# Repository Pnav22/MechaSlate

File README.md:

# MechaSlate 
**A Custom-Built Mechanical Keyboard**  
by Pranav M

---

## Overview
**MechaSlate** is my first custom mechanical keyboard project, created from scratch with no prior experience. This build taught me PCB design using KiCad, CAD modeling with Fusion 360, and the use of plugins and scripts to place keyswitches

[Watch on YouTube](https://www.youtube.com/shorts/u8ZRRqsj9ko)

I wanted to make this project so I could learn more about electronics and familiarize myself with more forms of engineering. It was really fun!
---

####  Initial Layout Planning
I decided on I wanted to make a keyboard like this 

#### PCB Design

| Schematic |  PCB |
|:--:|:--:|
|  |  |

#### Case Design 
Back and front case modeled for print.

| Back | Front |
|:--:|:--:|
| |  |

Added a staggering Slot pattern for the back!

####  Final Case
Manually placed all keycaps and installed everything.

---

#### Assembly 

It uses **threaded heat-set inserts (M3 x 5mm x 4mm)** for secure mounting. These inserts are installed into the case.

The top and bottom halves of the keyboard are fastened together using **four M3 x 16mm socket head cap screws .

This project has a Gasket Mount 

| Item Name            | Item Source | Quantity | Cost (USD w/ shipping) | Link |
|----------------------|-------------|----------|-------------------------|------|
| [Akko V3 Creamy Blue](https://www.amazon.com/Keyboard-Switch-Dustproof-Mechanical-Tactile-Switches/dp/B0C3H7PR1Z/ref=sr_1_2?crid=3V8ZPHA61P1MI&dib=eyJ2IjoiMSJ9.fKBr5G4iSMtdTKbGCum4GTBxYhCkemfukSXdnXwlOggG5oUsWwYAkdNtq9D0iMtFWSFib3KoufBG9x8I5c5MVUElE49E3UFhJKIZ3ApsSM-5lvnFfwzDVzr6UqqM9poQk2m3qxSxbyNIokBwpc6-MH-W-xoeoUtm8VAZ283vHpdD6ug9pvK7o0DDKZvxSUEk65CaZ0EXJkd1_wkjwBl1uJF0N5W6FdGn0ADwHfifVrA.90b59dVQxtPg1F6tWS84BnlJyIl1gNKa-D9l9R-ZRBo&dib_tag=se&keywords=mechanical%2Bswitches&qid=1750895537&sprefix=mechanical%2Bswitche%2Caps%2C130&sr=8-2&th=1) | Amazon | 80 | $30.98 | ✔️ |
| [PCB x5 (min quantity)]() | JLCPCB | – | $35.00 | ✔️ |
| [1N4148 Diodes](https://www.amazon.com/120Pcs-Rectifier-100Volt-Electronic-Silicon/dp/B0DN62QFYS/ref=sr_1_2?crid=1NZP4MAKACY15&dib=eyJ2IjoiMSJ9.8C1ebcszlPAbe4ldgX4jaM9nlgUAEZPfJqUMbjw_ZdqFKxpnIivj_Z4cD5uV-gtOvZBRazL-E3Q1E3eIT-Ftjfa-M9u06JHbpagrebY6wR-MjXtE1g2eBqvQ9QfL5Z_cTC2qNZDhdzfQsdHBOuk4NguB0ZzVxi_ZnOogCMsG99KTpR-rOWwd8dx9r3WikMGhAXj6ucuVXPIyicNVLnkdmw5zp6bgk_T0abfg_QhSpIk.yLjXK7wRlg-Hz0BfUQS_emE2Fbb75e3WeWxR9YOZ8y0&dib_tag=se&keywords=1n4148%2Bdiode&qid=1750895805&sprefix=1N4148%2B%2Caps%2C134&sr=8-2&th=1) | Amazon | 80 | $5.00 | ✔️ |
| [Durock V3 Stabilizers](https://www.amazon.com/DUROCK-Stabilizer-Innovative-Pre-clipped-Stabilizers/dp/B0CTHNZWN5/ref=sr_1_2?crid=2YND75THDZ71R&dib=eyJ2IjoiMSJ9.9YfniIYaI-o34quoUu90m3IVLkb4CNwyUl-SF8Fa0k30TPJD2oXjwvplYKLUvzz5oBOeM0fKrU5epHnFkPKzpaeCa2pE7aeqGZCMdcpq5P3N24mrE2Wy7Mu9ZeUTCEQjblblRVyfnqsjdvppAg5TxKPo_RuBAgn2zEmaJQvSTe4phoVZpAuzQXckSCATkHQf1teP9mYFuBXbdWuhYxIs8tDTrkJdPAxXpRpw2YnIhDc.6Kj9YbwQpDxJUeGeAAW4wsdQlsfZg6llBKqjkAUyMjQ&dib_tag=se&keywords=Durock%2BV3%2BStabilizers&qid=1750895835&sprefix=durock%2Bv3%2Bstabilizers%2Caps%2C136&sr=8-2&th=1) | Amazon | 8 | $15.00 | ✔️ |
| [Heatset Inserts](https://www.amazon.com/Threaded-Inserts-Soldering-Printed-Materials/dp/B0D7M3LJDL/ref=sr_1_1?crid=3QZDBQXSKRU35&dib=eyJ2IjoiMSJ9.TwXOi20xgBRd0n6qYM1WhV77xBk-3OSrIR2iz97DqR-zHLno-iLJif7tALJYQQG0uBneqK91YwYKwlOy8VACWcxlYHq9SkNRcOzNTHUaqBlkn0XEFOlVw_hkG1YHrU4i_o1rC7-dxaXwGvNd4M2CQ01mVR0tAPXtc9kX-9cozYncDvfSlINvCWy4xUOvBKtPHRdf_f9zduAmGxicl6vt1bSo2uvhSrKc4KHI-Kr5sgo.3IrV-xt1TwdcPG-fDb_L3T_gU6rrWeTdcYyxAc10u7E&dib_tag=se&keywords=heatset%2Binserts%2Bm3&qid=1750895904&sprefix=heatset%2Binserts%2Bm%2Caps%2C127&sr=8-1&th=1) | Amazon | 4 | $7.00 | ✔️ |
| [Nice_Nano_V2](https://www.amazon.com/AITRIP-Development-Bluetooth-Management-Module%EF%BC%8CNano/dp/B0DCZJKYL1/ref=sr_1_1?crid=2DO3PWHLDKPBU&dib=eyJ2IjoiMSJ9.r1x7MrhEmzjZsjVM-WVZleRI46Xy1yf3SpHt_AOgLDRhQc2ErkSjyVMLVjaL_qQsggobMgZJk8u8nVifN1DM3-2QyfhgCzRAdTgsoaWe6ibA8fY9VC4V8xYi2rafTrbHL3LLoKlgxQjito2Hluo4dr-XRpCPRyB061eb9TpGqa22AcU-vi0IQ81lLb8XLP9J6FHsi5dxECTH0_K2hZQEmCWnvypa8UxT0GPsB0t1uVA.cCG4lu1GNZcAlBXO1QaydRfsgY11n8NoO3NpEclm1a0&dib_tag=se&keywords=Nice_Nano_V2&qid=1750895977&sprefix=nice_nano_v2%2Caps%2C186&sr=8-1) | Amazon | 1 | $15.00 | ✔️ |
| [Keycaps](https://www.amazon.com/Keycaps-Doubleshot-Percent-Mechanical-Keyboard/dp/B0D1QVD55F/ref=sr_1_1?crid=2C83SKJ6IXOXQ&dib=eyJ2IjoiMSJ9.zEkcyt2autzMfJSmHiztLDvsxSmTtl97hkaq48-kgPoHbughJEeKreEhJIEldYH3aM7OfiiExIYq_OAMcjgLLZ75HwHDwg4lovccHK-NovY9--uDyJ7HKFVWYXG6f1EfNY0OGP-bxX-KKSpcmeT7ZrV3m_1VvwEMMxk3OQNFfQtBOfElMc8EmS1GXqCL8FJ-T8rQlqWWOT_g3K-vA3c8Nx8Y8aIl8e5MjLYiDg3Z3Dw.LSbk542b5PjWgET1ma7ldn8C6btV93Q9RSVqV7RanHY&dib_tag=se&keywords=keycaps&qid=1750895995&sprefix=keycaps%2Caps%2C145&sr=8-1&th=1) | Amazon | 80 | $18.00 | ✔️ |

**Total Cost:** **$125.98**

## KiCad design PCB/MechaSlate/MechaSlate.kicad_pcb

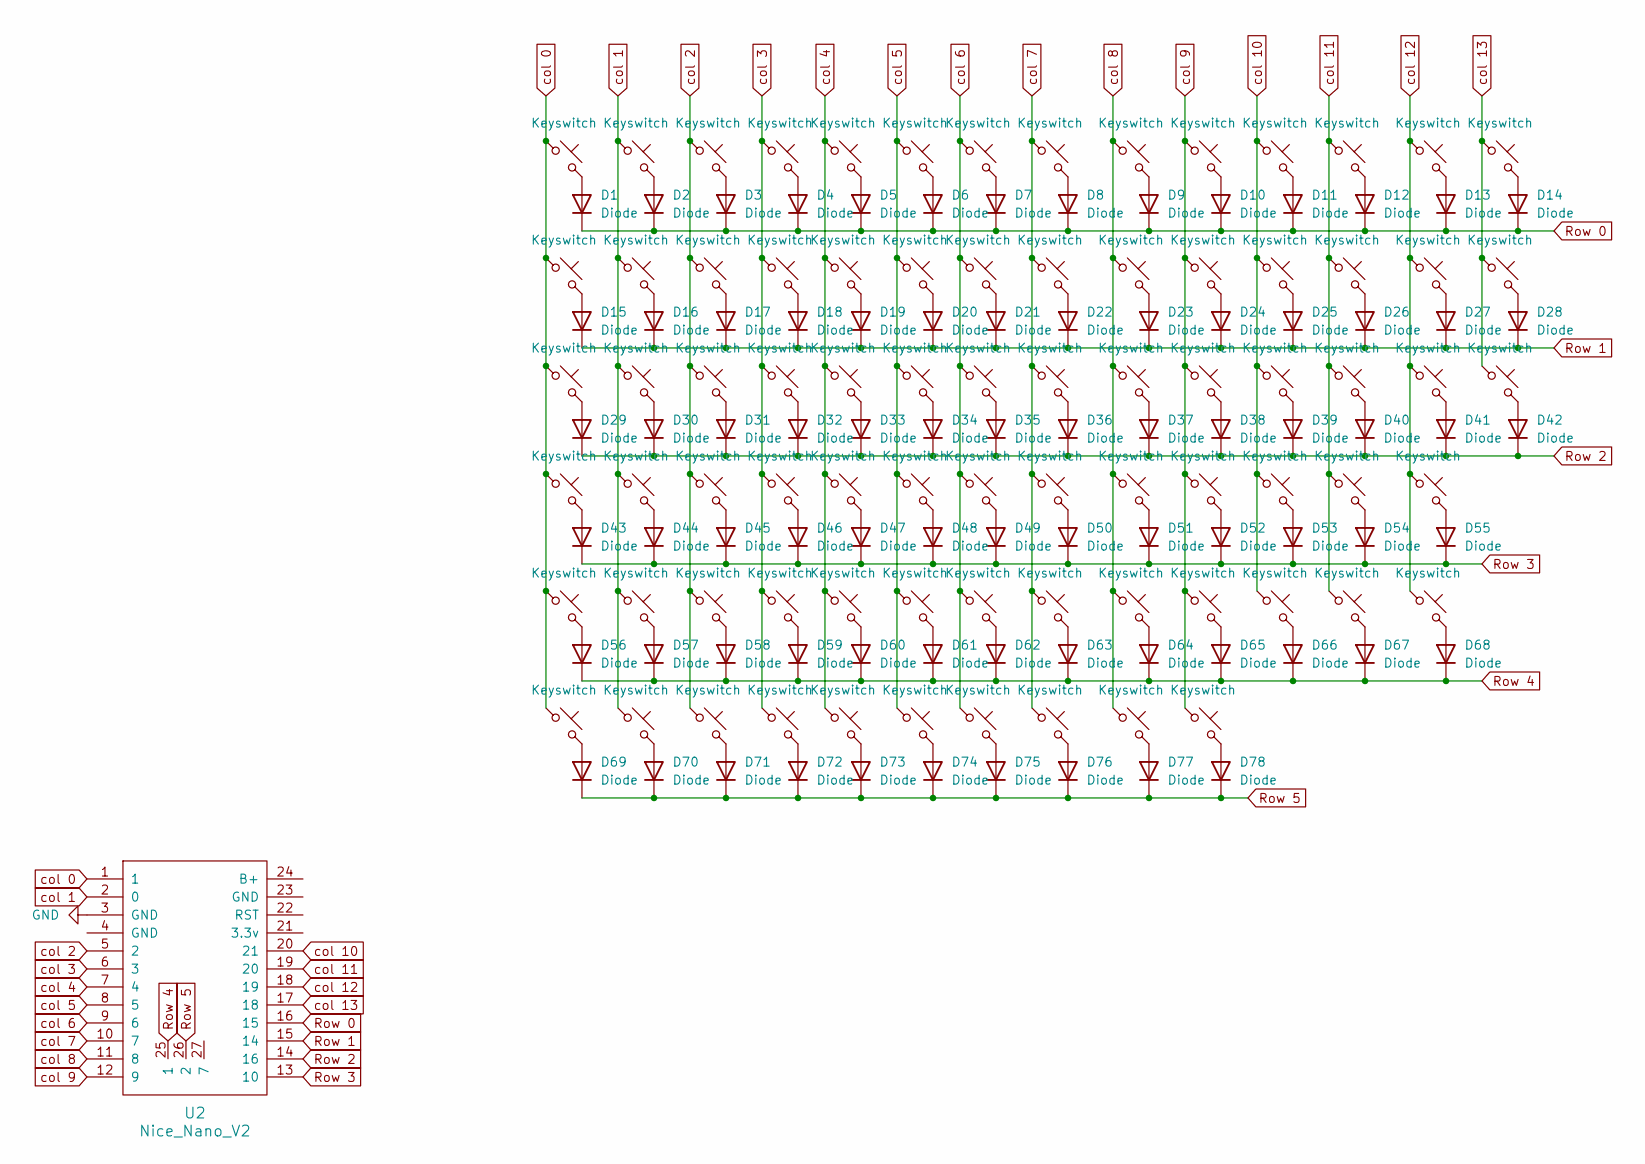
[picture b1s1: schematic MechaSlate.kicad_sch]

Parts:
D1, D2, D3, D4, D5, D6, D7, D8, D9, D10, D11, D12, D13, D14, D15, D16, D17, D18, D19, D20, D21, D22, D23, D24, D25, D26, D27, D28, D29, D30, D31, D32, D33, D34, D35, D36, D37, D38, D39, D40, D41, D42, D43, D44, D45, D46, D47, D48, D49, D50, D51, D52, D53, D54, D55, D56, D57, D58, D59, D60, D61, D62, D63, D64, D65, D66, D67, D68, D69, D70, D71, D72, D73, D74, D75, D76, D77, D78: Diode; Diode_DO-35
S1, S2, S3, S4, S5, S6, S7, S8, S9, S10, S11, S12, S13, S14, S15, S16, S17, S18, S19, S20, S21, S22, S23, S24, S25, S26, S27, S28, S29, S30, S31, S32, S33, S34, S35, S36, S37, S38, S39, S40, S41, S42, S43, S44, S45, S46, S47, S48, S49, S50, S51, S52, S53, S54, S55, S56, S57, S58, S59, S60, S61, S62, S63, S64, S65, S66, S67, S68, S69, S70, S71, S72, S73, S74, S75, S76, S77, S78: Keyswitch; SW_Cherry_MX_1.00u_PCB
U2: Nice_Nano_V2

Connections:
GND: U2.3 (GND)
unnamed: D1.2 (A), S1.2
unnamed: D2.2 (A), S2.2
unnamed: D3.2 (A), S3.2
unnamed: D4.2 (A), S4.2
unnamed: D5.2 (A), S5.2
unnamed: D6.2 (A), S6.2
unnamed: D7.2 (A), S7.2
unnamed: D8.2 (A), S8.2
unnamed: D9.2 (A), S9.2
unnamed: D10.2 (A), S10.2
unnamed: D11.2 (A), S11.2
unnamed: D12.2 (A), S12.2
unnamed: D13.2 (A), S13.2
unnamed: D14.2 (A), S14.2
unnamed: D15.2 (A), S15.2
unnamed: D16.2 (A), S16.2
unnamed: D17.2 (A), S17.2
unnamed: D18.2 (A), S18.2
unnamed: D19.2 (A), S19.2
unnamed: D20.2 (A), S20.2
unnamed: D21.2 (A), S21.2
unnamed: D22.2 (A), S22.2
unnamed: D23.2 (A), S23.2
unnamed: D24.2 (A), S24.2
unnamed: D25.2 (A), S25.2
unnamed: D26.2 (A), S26.2
unnamed: D27.2 (A), S27.2
unnamed: D28.2 (A), S28.2
unnamed: D29.2 (A), S29.2
unnamed: D30.2 (A), S30.2
unnamed: D31.2 (A), S31.2
unnamed: D32.2 (A), S32.2
unnamed: D33.2 (A), S33.2
unnamed: D34.2 (A), S34.2
unnamed: D35.2 (A), S35.2
unnamed: D36.2 (A), S36.2
unnamed: D37.2 (A), S37.2
unnamed: D38.2 (A), S38.2
unnamed: D39.2 (A), S39.2
unnamed: D40.2 (A), S40.2
unnamed: D41.2 (A), S41.2
unnamed: D42.2 (A), S42.2
unnamed: D43.2 (A), S43.2
unnamed: D44.2 (A), S44.2
unnamed: D45.2 (A), S45.2
unnamed: D46.2 (A), S46.2
unnamed: D47.2 (A), S47.2
unnamed: D48.2 (A), S48.2
unnamed: D49.2 (A), S49.2
unnamed: D50.2 (A), S50.2
unnamed: D51.2 (A), S51.2
unnamed: D52.2 (A), S52.2
unnamed: D53.2 (A), S53.2
unnamed: D54.2 (A), S54.2
unnamed: D55.2 (A), S55.2
unnamed: D56.2 (A), S56.2
unnamed: D57.2 (A), S57.2
unnamed: D58.2 (A), S58.2
unnamed: D59.2 (A), S59.2
unnamed: D60.2 (A), S60.2
unnamed: D61.2 (A), S61.2
unnamed: D62.2 (A), S62.2
unnamed: D63.2 (A), S63.2
unnamed: D64.2 (A), S64.2
unnamed: D65.2 (A), S65.2
unnamed: D66.2 (A), S66.2
unnamed: D67.2 (A), S67.2
unnamed: D68.2 (A), S68.2
unnamed: D69.2 (A), S69.2
unnamed: D70.2 (A), S70.2
unnamed: D71.2 (A), S71.2
unnamed: D72.2 (A), S72.2
unnamed: D73.2 (A), S73.2
unnamed: D74.2 (A), S74.2
unnamed: D75.2 (A), S75.2
unnamed: D76.2 (A), S76.2
unnamed: D77.2 (A), S77.2
unnamed: D78.2 (A), S78.2
Row 0: D1.1 (K), D2.1 (K), D3.1 (K), D4.1 (K), D5.1 (K), D6.1 (K), D7.1 (K), D8.1 (K), D9.1 (K), D10.1 (K), D11.1 (K), D12.1 (K), D13.1 (K), D14.1 (K), U2.16 (15)
Row 1: D15.1 (K), D16.1 (K), D17.1 (K), D18.1 (K), D19.1 (K), D20.1 (K), D21.1 (K), D22.1 (K), D23.1 (K), D24.1 (K), D25.1 (K), D26.1 (K), D27.1 (K), D28.1 (K), U2.15 (14)
Row 2: D29.1 (K), D30.1 (K), D31.1 (K), D32.1 (K), D33.1 (K), D34.1 (K), D35.1 (K), D36.1 (K), D37.1 (K), D38.1 (K), D39.1 (K), D40.1 (K), D41.1 (K), D42.1 (K), U2.14 (16)
Row 3: D43.1 (K), D44.1 (K), D45.1 (K), D46.1 (K), D47.1 (K), D48.1 (K), D49.1 (K), D50.1 (K), D51.1 (K), D52.1 (K), D53.1 (K), D54.1 (K), D55.1 (K), U2.13 (10)
Row 4: D56.1 (K), D57.1 (K), D58.1 (K), D59.1 (K), D60.1 (K), D61.1 (K), D62.1 (K), D63.1 (K), D64.1 (K), D65.1 (K), D66.1 (K), D67.1 (K), D68.1 (K), U2.25 (1)
Row 5: D69.1 (K), D70.1 (K), D71.1 (K), D72.1 (K), D73.1 (K), D74.1 (K), D75.1 (K), D76.1 (K), D77.1 (K), D78.1 (K), U2.26 (2)
col 0: S1.1, S15.1, S29.1, S43.1, S56.1, S69.1, U2.1
col 1: S2.1, S16.1, S30.1, S44.1, S57.1, S70.1, U2.2 (0)
col 2: S3.1, S17.1, S31.1, S45.1, S58.1, S71.1, U2.5 (2)
col 3: S4.1, S18.1, S32.1, S46.1, S59.1, S72.1, U2.6 (3)
col 4: S5.1, S19.1, S33.1, S47.1, S60.1, S73.1, U2.7 (4)
col 5: S6.1, S20.1, S34.1, S48.1, S61.1, S74.1, U2.8 (5)
col 6: S7.1, S21.1, S35.1, S49.1, S62.1, S75.1, U2.9 (6)
col 7: S8.1, S22.1, S36.1, S50.1, S63.1, S76.1, U2.10 (7)
col 8: S9.1, S23.1, S37.1, S51.1, S64.1, S77.1, U2.11 (8)
col 9: S10.1, S24.1, S38.1, S52.1, S65.1, S78.1, U2.12 (9)
col 10: S11.1, S25.1, S39.1, S53.1, S66.1, U2.20 (21)
col 11: S12.1, S26.1, S40.1, S54.1, S67.1, U2.19 (20)
col 12: S13.1, S27.1, S41.1, S55.1, S68.1, U2.18 (19)
col 13: S14.1, S28.1, S42.1, U2.17 (18)

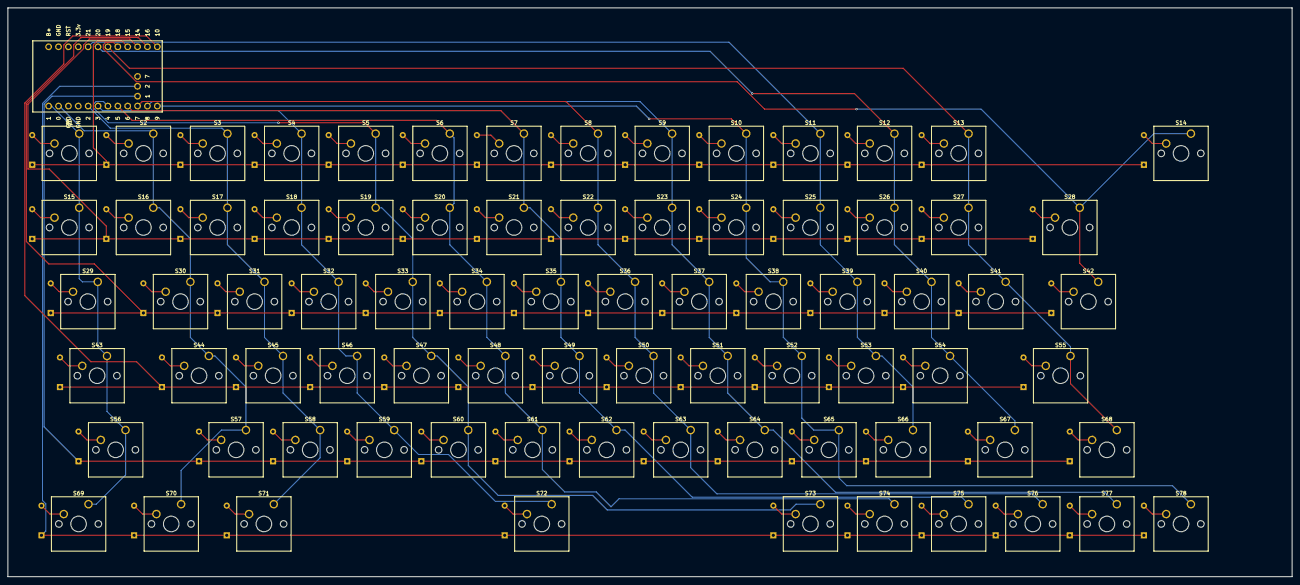
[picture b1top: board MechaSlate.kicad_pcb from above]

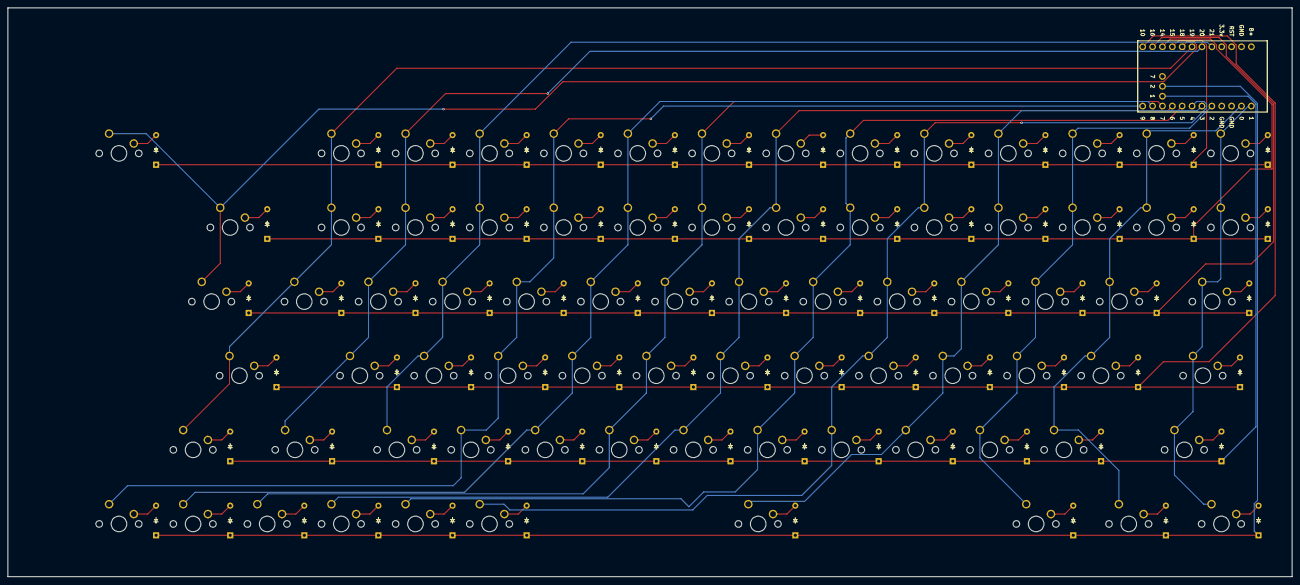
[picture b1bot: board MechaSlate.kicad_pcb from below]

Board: 2 copper layers, 330.1 x 146.2 mm, 157 parts (78 on the bottom side), 98 nets.

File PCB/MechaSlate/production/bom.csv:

Designator,Footprint,Quantity,Value,LCSC Part #
"D1, D10, D11, D12, D13, D14, D15, D16, D17, D18, D19, D2, D20, D21, D22, D23, D24, D25, D26, D27, D28, D29, D3, D30, D31, D32, D33, D34, D35, D36, D37, D38, D39, D4, D40, D41, D42, D43, D44, D45, D46, D47, D48, D49, D5, D50, D51, D52, D53, D54, D55, D56, D57, D58, D59, D6, D60, D61, D62, D63, D64, D65, D66, D67, D68, D69, D7, D70, D71, D72, D73, D74, D75, D76, D77, D78, D8, D9",Diode_DO-35,78,Diode,
"S1, S10, S11, S12, S13, S14, S15, S16, S17, S18, S19, S2, S20, S21, S22, S23, S24, S25, S26, S27, S28, S29, S3, S30, S31, S32, S33, S34, S35, S36, S37, S38, S39, S4, S40, S41, S42, S43, S44, S45, S46, S47, S48, S49, S5, S50, S51, S52, S53, S54, S55, S56, S57, S58, S59, S6, S60, S61, S62, S63, S64, S65, S66, S67, S68, S69, S7, S70, S71, S72, S73, S74, S75, S76, S77, S78, S8, S9",SW_Cherry_MX_1.00u_PCB,78,Keyswitch,
U2,Nice_Nano_V2,1,Nice_Nano_V2,

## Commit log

2025-06-25 Create Journal
2025-06-26 Added stuff
2025-06-26 added pcb
2025-06-26 added source files pcb
2025-06-28 More changes to CAD
2025-06-28 Changed Cad
